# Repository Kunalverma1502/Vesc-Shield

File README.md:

# ⚡️Vesc-Shield 

The Vesc-Shield is a remarkable open-source shield designed for effortless integration with the [Flipsky Vesc 6.7 Pro](https://flipsky.net/products/flipsky-mini-fsesc6-7-pro-70a-base-on-vesc6-6-with-aluminum-anodized-heat-sink?variant=42664011956465&currency=USD&utm_medium=product_sync&utm_source=google&utm_content=sag_organic&utm_campaign=sag_organic&gad=1&gclid=CjwKCAjwo9unBhBTEiwAipC110jtGEOlnNmrO9Tqul8LjfJ8Tr05fPZSuTm81KGfPlVTePEtUpiYyBoCPOYQAvD_BwE). By doing so, it enables cost-effective utilization in a wide range of robotic applications while affording precise driver control through the seamless integration of Dspace.

# Features 
1. **Enhanced Motor Encoder Output:** Amplifies motor encoder output signals for both Vesc and Dspace, ensuring optimal performance and precision.<br/>
1. **Effortless Position Reset:** Facilitates easy and precise index position resetting, whether through digital or manual methods.<br/>
1. **Motor Driver Control:** Provides the capability to enable or disable the motor driver with simplicity and efficiency.<br/>
1. **Streamlined Connectivity:** Utilizes a single ribbon cable connection to Dspace, consolidating all essential signals for a tidy and efficient setup.<br/>
1. **Informative LEDs:** Equipped with LEDs that display vital information, including power status, enable/disable status, and index reset, ensuring at-a-glance monitoring and feedback.<br/>

# Schematics

<br/>
<br/>

# Board

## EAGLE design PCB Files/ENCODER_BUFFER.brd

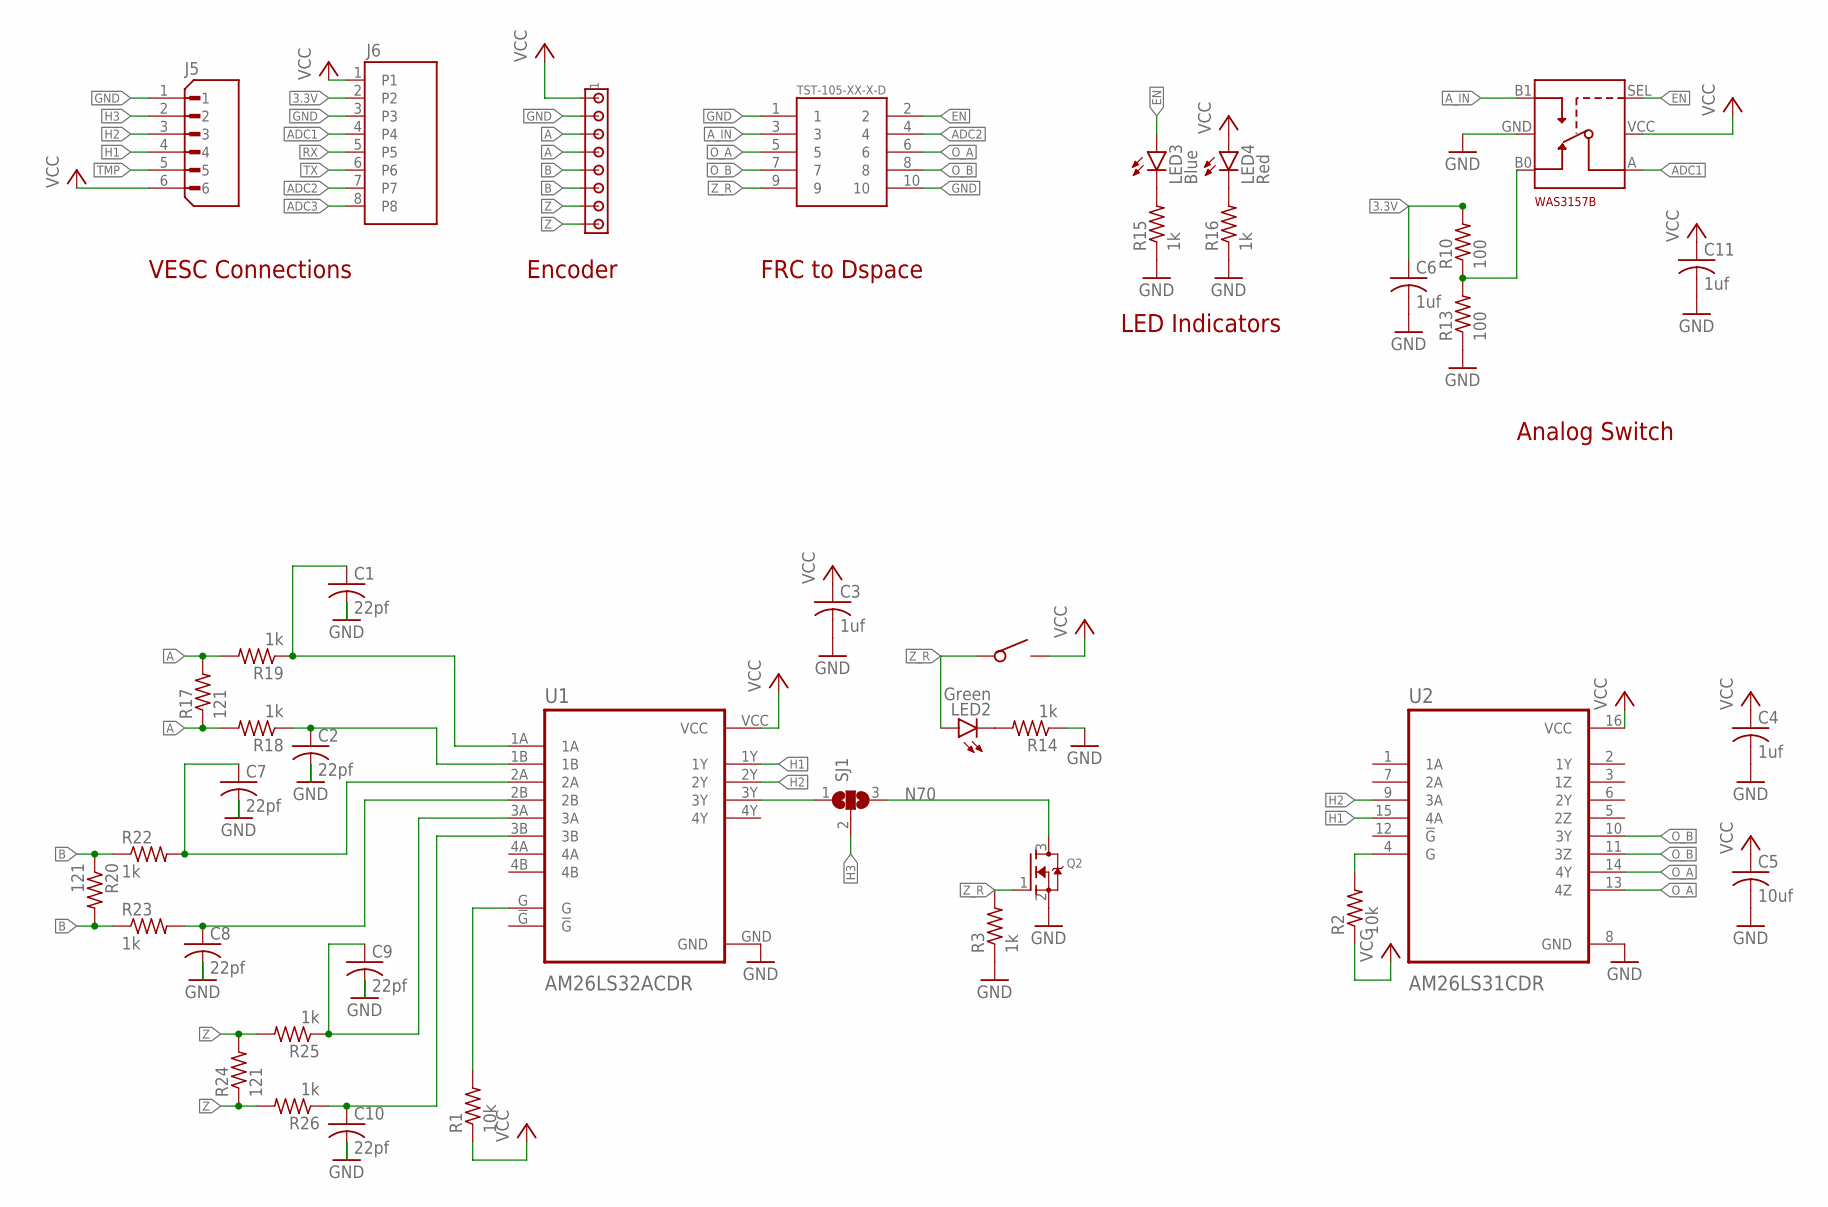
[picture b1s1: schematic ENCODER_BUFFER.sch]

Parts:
C1, C2, C7, C8, C9, C10: 22pf; C0402
C3, C4, C6, C11: 1uf; C0402
C5: 10uf; C0402
J2: TST-105-XX-X-D
J3: MTA08-100; 10X08MTA
J5: B6B-PH-K-S(LF)(SN); JST_B6B-PH-K-S(LF)(SN)
J6: B8B-PH-K-S(LF)(SN); JST_B8B-PH-K-S(LF)(SN)
LED2: Green; CHIPLED_0603
LED3: Blue; CHIPLED_0603
LED4: Red; CHIPLED_0603
Q2: MOSFET-NREFLOW; SOT23
R1, R2: 10k; R0402
R3, R14, R15, R16, R18, R19, R22, R23, R25, R26: 1k; R0402
R10, R13: 100; R0402
R17, R20, R24: 121; R0402
SJ1: SJ2W; SJ_2
U1: AM26LS32ACDR; SOIC127P600X175-16N
U2: AM26LS31CDR; SOIC127P600X175-16N
U3: WAS3157BUMT6; UMT6
U$1: TS-1088-AR02016; SMD

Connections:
3.3V: C6.1, J6.2, R10.2
3Y: SJ1.1, U1.3Y
!A: J3.4, R17.1, R18.2
!B: J3.6, R20.2, R23.1
!Z: J3.8, R24.1, R26.2
A: J3.3, R17.2, R19.2
ADC1: J6.4, U3.A
ADC2: J2.4, J6.7
ADC3: J6.8
A_IN: J2.3, U3.B1
B: J3.5, R20.1, R22.1
EN: J2.2, LED3.A, U3.SEL
GND: C1.2, C2.2, C3.2, C4.2, C5.2, C6.2, C7.2, C8.2, C9.2, C10.2, C11.2, J2.1, J2.10, J3.2, J5.1, J6.3, Q2.2 (S), R3.1, R13.1, R14.1, R15.1, R16.1, U1.GND, U2.8 (GND), U3.GND
H1: J5.4, U1.1Y, U2.15 (4A)
H2: J5.3, U1.2Y, U2.9 (3A)
H3: J5.2, SJ1.2
N70: Q2.3 (D), SJ1.3
unnamed: C1.1, R19.1, U1.1A
unnamed: C2.1, R18.1, U1.1B
unnamed: R1.2, U1.G
unnamed: R10.1, R13.2, U3.B0
unnamed: C8.1, R23.2, U1.2B
unnamed: C7.1, R22.2, U1.2A
unnamed: LED2.C, R14.2
unnamed: LED3.C, R15.2
unnamed: LED4.C, R16.2
unnamed: R2.2, U2.4 (G)
unnamed: C9.1, R25.1, U1.3A
unnamed: C10.1, R26.1, U1.3B
O_!A: J2.5, U2.13 (4Z)
O_!B: J2.7, U2.11 (3Z)
O_A: J2.6, U2.14 (4Y)
O_B: J2.8, U2.10 (3Y)
RX: J6.5
TMP: J5.5
TX: J6.6
VCC: C3.1, C4.1, C5.1, C11.1, J3.1, J5.6, J6.1, LED4.A, R1.1, R2.1, U1.VCC, U2.16 (VCC), U3.VCC, U$1.P$2
Z: J3.7, R24.2, R25.2
Z_R: J2.9, LED2.A, Q2.1 (G), R3.2, U$1.P$1

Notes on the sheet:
WAS3157B
VESC Connections
Encoder
FRC to Dspace
LED Indicators
Analog Switch

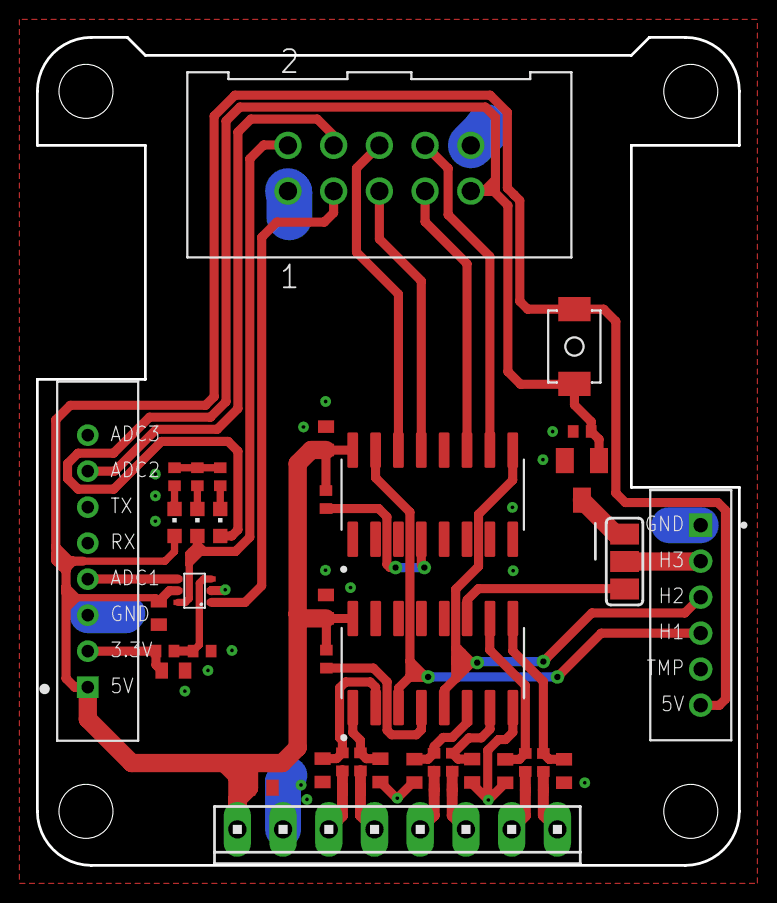
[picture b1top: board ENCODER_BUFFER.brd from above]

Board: 2 copper layers, 39.0 x 46.0 mm, 41 parts (0 on the bottom side), 35 nets.

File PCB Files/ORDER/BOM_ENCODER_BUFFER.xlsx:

Comment | Designator | Footprint | JLCPCB Part #（optional）
SI2300 | Q2 | SOT-23 | C2985622
100 | R10, R13 | R0402 | C325391
10k | R1, R2 | R0402 | C375970
10uf | C5 | C0402 | C703695
121 | R17, R20, R24 | R0402 | C25080
1k | R3, R14, R15, R16, R18, R19, R22, R23, R25, R26 | R0402 | C306197
1uf | C3, C4, C6, C11 | C0402 | C415694
22pf | C1, C2, C7, C8, C9, C10 | C0402 | C694268
AM26LS31CDR | U2 | SOIC-16 | C6179
AM26LS32ACDR | U1 | SOIC-16 | C6180
19-213UYOC/S530-A3/TR8 | LED3 | 603 | C264452
19-21/GHC-YR1S2M/3T | LED2 | 603 | C605453
TJ-S1608SW6TDSLC2R2G-A5 | LED4 | 603 | C601671
TS-1088-AR02016 | U$1 | SMD | C720477
WAS3157B-6/TR | U3 | SOT-363 | C213161

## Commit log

2023-09-06 README.md
